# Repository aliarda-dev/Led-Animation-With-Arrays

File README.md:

***Arduino LED Array Project***

Bu proje, Akdeniz Üniversitesi Elektrik-Elektronik Mühendisliği 1. sınıf öğrencisi olarak Arduino kullanarak yaptığım ilk projem, C programlama dilindeki dizi (array) ve döngü (loop) mantığını fiziksel bir devreye taşıdığım ilk çalışmamdır.

***Donanım***

* Arduino Uno

* 3x LED

* 3x 330Ω Direnç

***Öğrenim Kazanımları***

C dilindeki dizilerin donanım kontrolünde kullanımı.

Temel devre kurulumu ve ortak toprak (GND) hattı mantığı.

Gömülü sistemlere (Embedded Systems) giriş.

***Not*** 

Projenin dc güç kaynaklı,switch kullanılarak yapılacak halinin pcb tasarımı ve gerekli gerber dosyaları yüklendi.

### 🎥 Proje Demo Videosu

https://github.com/user-attachments/assets/f8f07f9c-d68f-4e64-a582-2faa462c132e

### 📷 Proje PCB Medyası

Ali Arda Kocabörek Akdeniz University | EEE Student# Led-Animation-With-Arrays

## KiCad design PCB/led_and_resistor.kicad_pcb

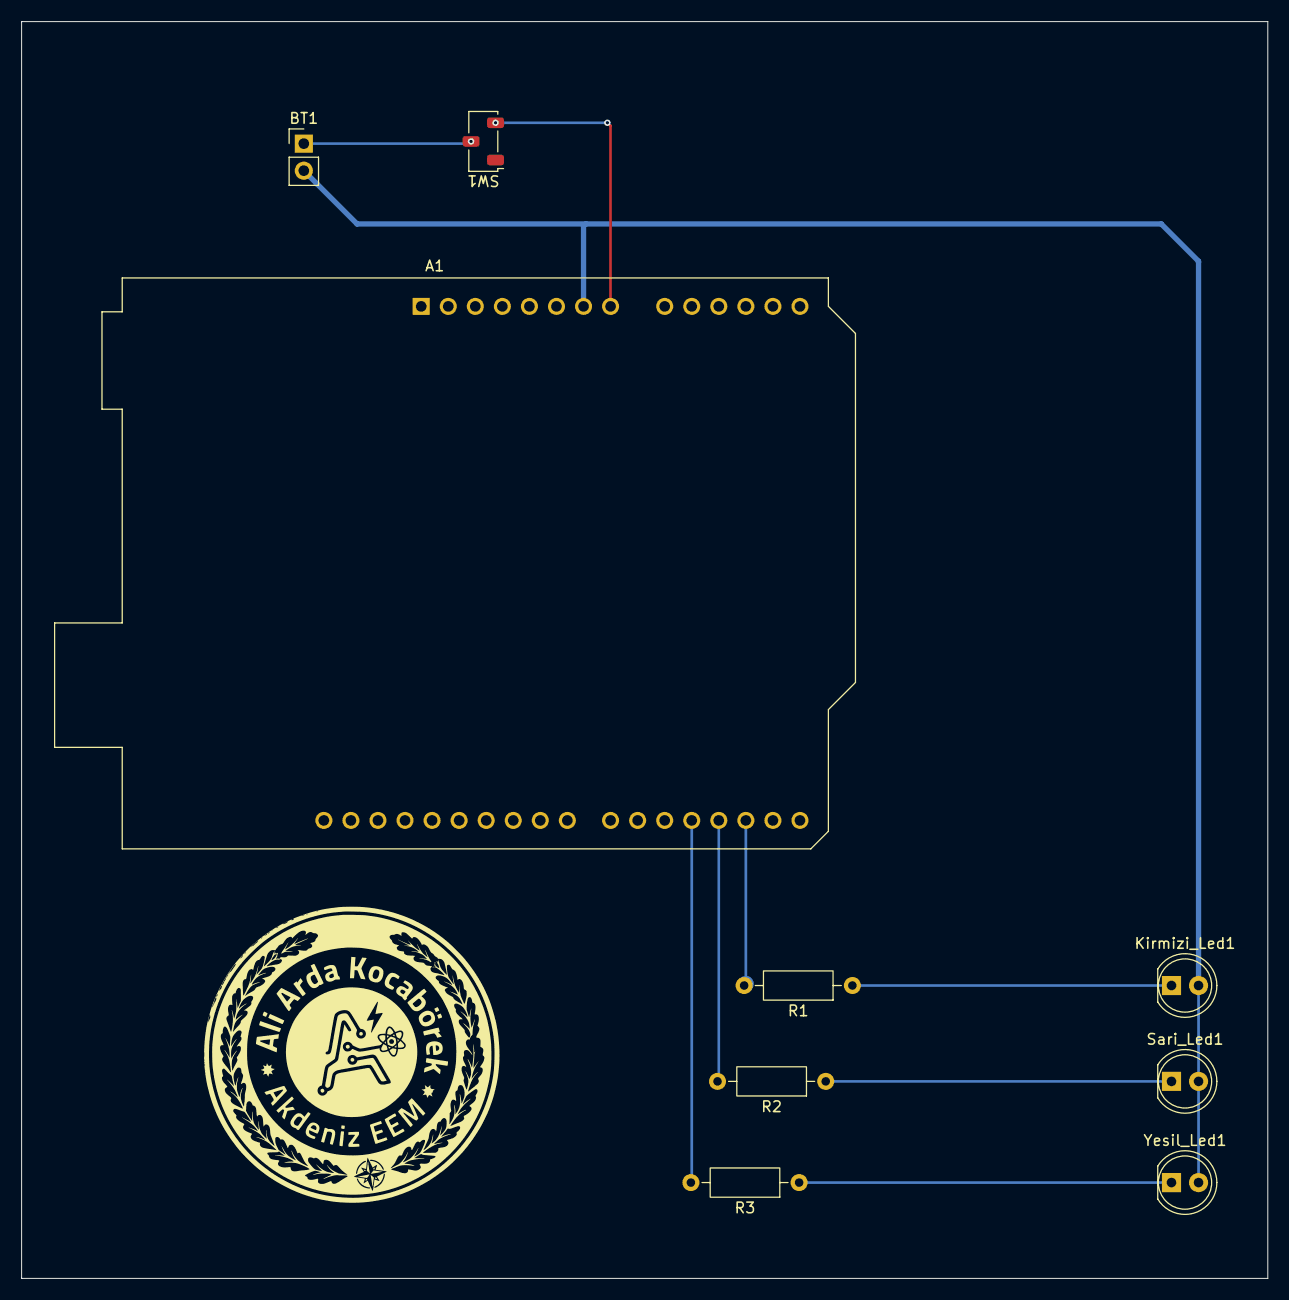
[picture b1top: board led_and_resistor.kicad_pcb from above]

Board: 2 copper layers, 117.0 x 118.0 mm, 9 parts (0 on the bottom side), 9 nets.

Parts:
A1: Arduino_UNO_R3
BT1: Battery_Cell; PinHeader_1x02_P2.54mm_Vertical
Kirmizi_Led1: D2; LED_D5.0mm
R1, R2, R3: 330R; R_Axial_DIN0207_L6.3mm_D2.5mm_P10.16mm_Horizontal
SW1: SW_Nidec_CAS-120A1; Nidec_Copal_CAS-120A
Sari_Led1: D3; LED_D5.0mm
Yesil_Led1: D4; LED_D5.0mm

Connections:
GND: A1.7 (GND), BT1.2 (-), Kirmizi_Led1.2 (A), Sari_Led1.2 (A), Yesil_Led1.2 (A)
K_Led: A1.17 (D2), R1.2
unnamed: BT1.1 (+), SW1.2 (B)
unnamed: Kirmizi_Led1.1 (K), R1.1
unnamed: R2.1, Sari_Led1.1 (K)
unnamed: R3.1, Yesil_Led1.1 (K)
S_Led: A1.18 (D3), R2.2
VCC: A1.8 (VIN), SW1.3 (A)
Y_Led: A1.19 (D4), R3.2

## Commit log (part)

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2026-02-12 About This Project
    Updated README to include project details and technical specifications.
2026-02-12 Code for project
2026-02-12 Arduino IDE Code for Led Array Project
2026-02-12 Project Description
2026-02-12 Project Overview
    Added a brief introduction about the project and learning outcomes.
2026-02-12 Added media
2026-02-12 Project Overview
    Added a section for project demo videos in the README.
2026-02-12 Project Overview
2026-02-12 Project Overview
    Updated project demo video link in README.
2026-02-14 About Led Animation With Arrays Project
2026-06-25 PCB for This Project
2026-06-25 Create dd
2026-06-25 Gerber Files for PCB
2026-06-25 PCB Files
